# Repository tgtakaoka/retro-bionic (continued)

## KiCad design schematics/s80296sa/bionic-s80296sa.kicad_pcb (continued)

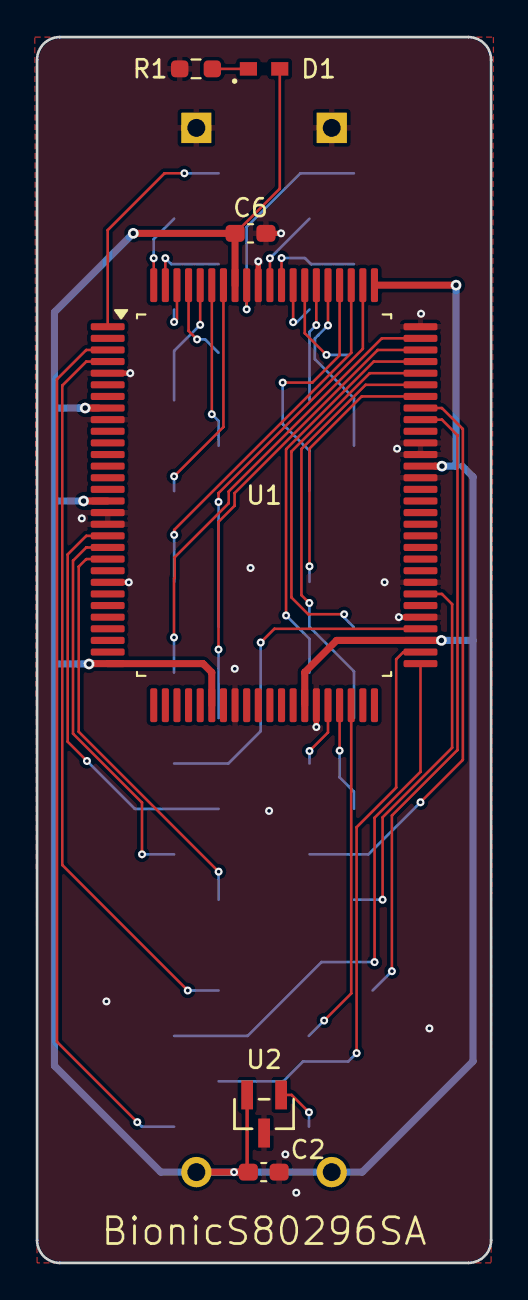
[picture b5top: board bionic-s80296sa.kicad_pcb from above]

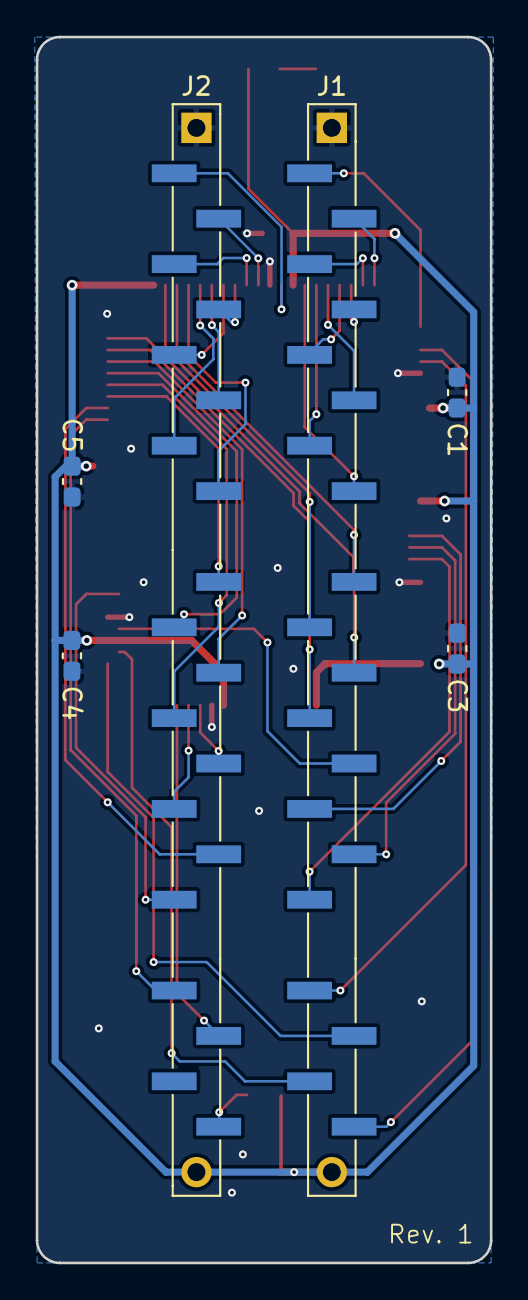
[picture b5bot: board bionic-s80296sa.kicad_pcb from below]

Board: 2 copper layers, 25.4 x 68.6 mm, 12 parts (6 on the bottom side), 42 nets.

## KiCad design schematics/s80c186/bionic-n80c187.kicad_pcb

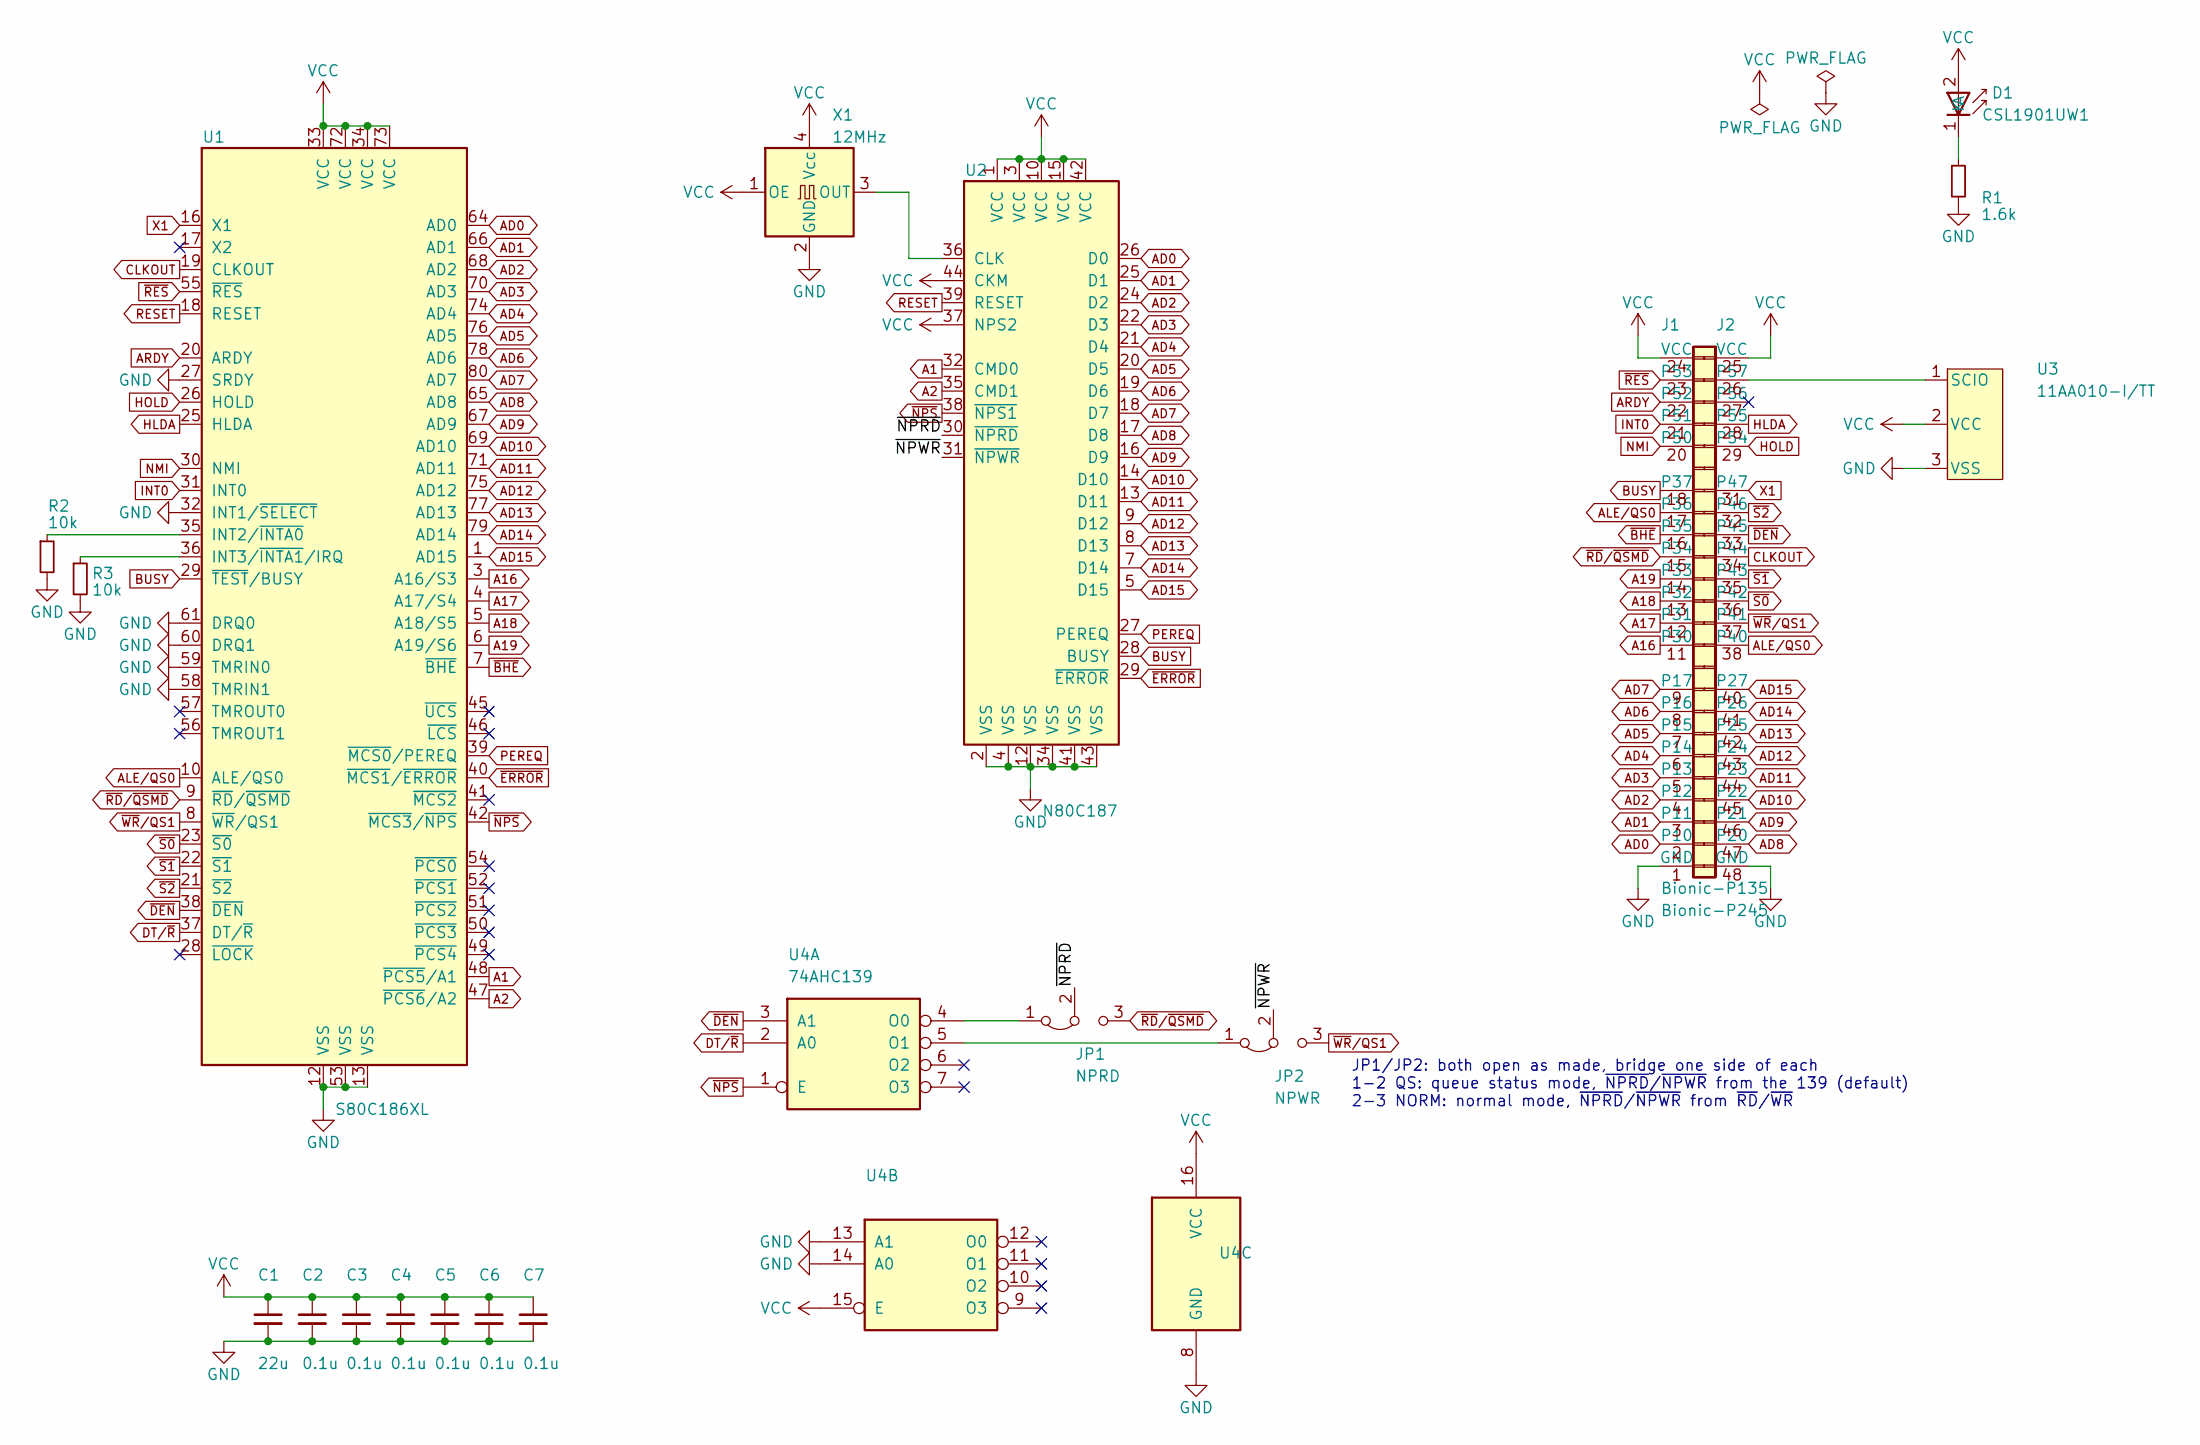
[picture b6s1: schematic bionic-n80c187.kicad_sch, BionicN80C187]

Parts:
C1: 22u; C_0603_1608Metric_Pad1.08x0.95mm_HandSolder
C2, C3, C4, C5, C6, C7: 0.1u; C_0603_1608Metric_Pad1.08x0.95mm_HandSolder
D1: CSL1901UW1; LED_CSL1901UW1_ROM-M
J1: Bionic-P135; Bionic-P135_SMT
J2: Bionic-P245; Bionic-P245_SMT
JP1: NPRD; SolderJumper-3_P2.0mm_Open_TrianglePad1.0x1.5mm_NumberLabels
JP2: NPWR; SolderJumper-3_P2.0mm_Open_TrianglePad1.0x1.5mm_NumberLabels
R1: 1.6k; R_0603_1608Metric_Pad0.98x0.95mm_HandSolder
R2, R3: 10k; R_0603_1608Metric_Pad0.98x0.95mm_HandSolder
U1: S80C186XL; QFP-80_14x20mm_P0.8mm_Intel
U2: N80C187; PLCC-44_SMD-Socket
U3: 11AA010-I/TT; SOT-23_MC_MCH-M
U4: 74AHC139; TSSOP-16_4.4x5mm_P0.65mm
X1: 12MHz; SX3M_3.2x2.5mm_HandSoldering

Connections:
/~NPRD: JP1.2 (C), U2.30 (~NPRD)
/~NPWR: JP2.2 (C), U2.31 (~NPWR)
A1: U1.48 (~PCS5/A1), U2.32 (CMD0)
A2: U1.47 (~PCS6/A2), U2.35 (CMD1)
A16: J1.11 (P30), U1.3 (A16/S3)
A17: J1.12 (P31), U1.4 (A17/S4)
A18: J1.13 (P32), U1.5 (A18/S5)
A19: J1.14 (P33), U1.6 (A19/S6)
AD0: J1.2 (P10), U1.64 (AD0), U2.26 (D0)
AD1: J1.3 (P11), U1.66 (AD1), U2.25 (D1)
AD2: J1.4 (P12), U1.68 (AD2), U2.24 (D2)
AD3: J1.5 (P13), U1.70 (AD3), U2.22 (D3)
AD4: J1.6 (P14), U1.74 (AD4), U2.21 (D4)
AD5: J1.7 (P15), U1.76 (AD5), U2.20 (D5)
AD6: J1.8 (P16), U1.78 (AD6), U2.19 (D6)
AD7: J1.9 (P17), U1.80 (AD7), U2.18 (D7)
AD8: J2.47 (P20), U1.65 (AD8), U2.17 (D8)
AD9: J2.46 (P21), U1.67 (AD9), U2.16 (D9)
AD10: J2.45 (P22), U1.69 (AD10), U2.14 (D10)
AD11: J2.44 (P23), U1.71 (AD11), U2.13 (D11)
AD12: J2.43 (P24), U1.75 (AD12), U2.9 (D12)
AD13: J2.42 (P25), U1.77 (AD13), U2.8 (D13)
AD14: J2.41 (P26), U1.79 (AD14), U2.7 (D14)
AD15: J2.40 (P27), U1.1 (AD15), U2.5 (D15)
ALE/QS0: J1.17 (P36), J2.38 (P40), U1.10 (ALE/QS0)
ARDY: J1.22 (P52), U1.20 (ARDY)
BUSY: J1.18 (P37), U1.29 (~TEST/BUSY), U2.28 (BUSY)
CLKOUT: J2.34 (P44), U1.19 (CLKOUT)
DT/~R: U1.37 (DT/~R), U4.2 (A0)
GND: C1.2, C2.2, C3.2, C4.2, C5.2, C6.2, C7.2, J1.1 (GND), J2.48 (GND), R1.2, R2.2, R3.2, U1.12 (VSS), U1.13 (VSS), U1.27 (SRDY), U1.32 (INT1/~SELECT), U1.53 (VSS), U1.58 (TMRIN1), U1.59 (TMRIN0), U1.60 (DRQ1), U1.61 (DRQ0), U2.2 (VSS), U2.4 (VSS), U2.12 (VSS), U2.34 (VSS), U2.41 (VSS), U2.43 (VSS), U3.3 (VSS), U4.8 (GND), U4.13 (A1), U4.14 (A0), X1.2 (GND)
HLDA: J2.28 (P55), U1.25 (HLDA)
HOLD: J2.29 (P54), U1.26 (HOLD)
INT0: J1.21 (P51), U1.31 (INT0)
NMI: J1.20 (P50), U1.30 (NMI)
unnamed: D1.1 (K), R1.1
unnamed: J2.26 (P57), U3.1 (SCIO)
unnamed: JP1.1 (A), U4.4 (O0)
unnamed: JP2.1 (A), U4.5 (O1)
unnamed: R2.1, U1.35 (INT2/~INTA0)
unnamed: R3.1, U1.36 (INT3/~INTA1/IRQ)
unnamed: U2.36 (CLK), X1.3 (OUT)
PEREQ: U1.39 (~MCS0/PEREQ), U2.27 (PEREQ)
RESET: U1.18 (RESET), U2.39 (RESET)
VCC: C1.1, C2.1, C3.1, C4.1, C5.1, C6.1, C7.1, D1.2 (A), J1.24 (VCC), J2.25 (VCC), U1.33 (VCC), U1.34 (VCC), U1.72 (VCC), U1.73 (VCC), U2.1 (VCC), U2.3 (VCC), U2.10 (VCC), U2.15 (VCC), U2.37 (NPS2), U2.42 (VCC), U2.44 (CKM), U3.2 (VCC), U4.15 (E), U4.16 (VCC), X1.1 (OE), X1.4 (Vcc)
X1: J2.31 (P47), U1.16 (X1)
~BHE: J1.16 (P35), U1.7 (~BHE)
~DEN: J2.33 (P45), U1.38 (~DEN), U4.3 (A1)
~ERROR: U1.40 (~MCS1/~ERROR), U2.29 (~ERROR)
~NPS: U1.42 (~MCS3/~NPS), U2.38 (~NPS1), U4.1 (E)
~RD/~QSMD: J1.15 (P34), JP1.3 (B), U1.9 (~RD/~QSMD)
~RES: J1.23 (P53), U1.55 (~RES)
~S0: J2.36 (P42), U1.23 (~S0)
~S1: J2.35 (P43), U1.22 (~S1)
~S2: J2.32 (P46), U1.21 (~S2)
~WR/QS1: J2.37 (P41), JP2.3 (B), U1.8 (~WR/QS1)

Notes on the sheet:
JP1/JP2: both open as made, bridge one side of each 1-2 QS: queue status mode, ~{NPRD}/~{NPWR} from the 139 (default) 2-3 NORM: normal mode, ~{NPRD}/~{NPWR} from ~{RD}/~{WR}

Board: 4 copper layers, 20 parts (12 on the bottom side), 55 nets, no tracks yet.

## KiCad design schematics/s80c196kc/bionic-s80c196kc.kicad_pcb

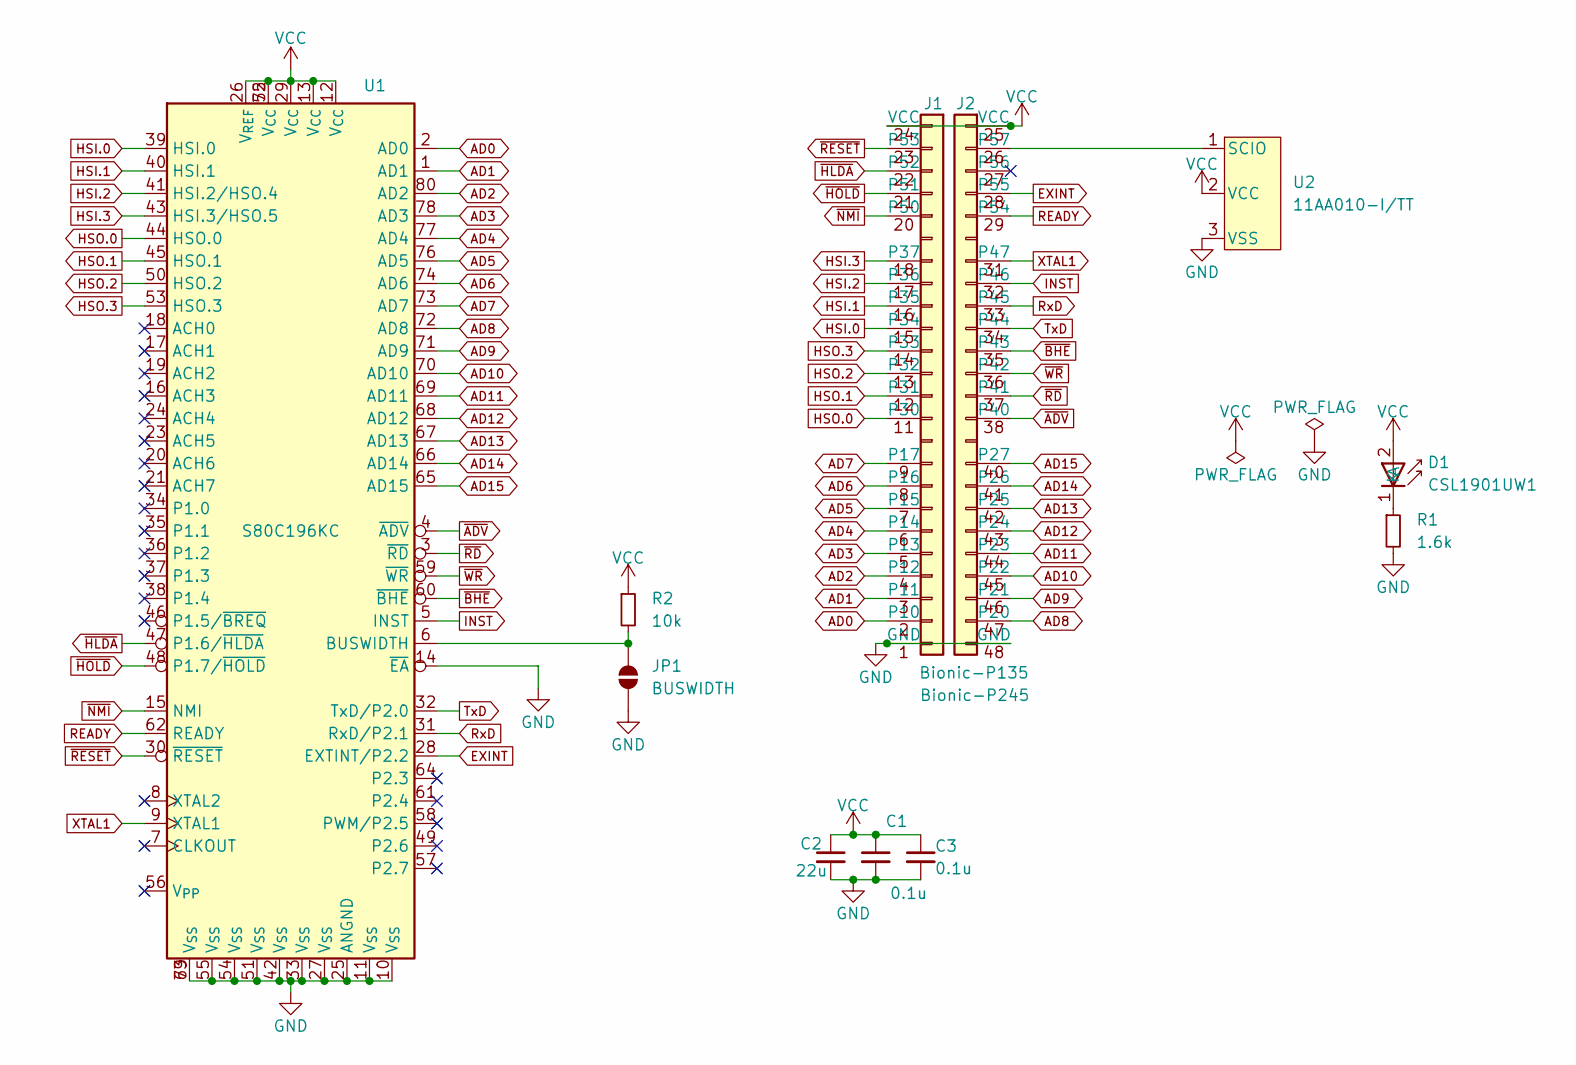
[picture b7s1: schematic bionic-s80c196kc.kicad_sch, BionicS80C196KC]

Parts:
C1, C3: 0.1u; C_0603_1608Metric_Pad1.08x0.95mm_HandSolder
C2: 22u; C_0603_1608Metric_Pad1.08x0.95mm_HandSolder
D1: CSL1901UW1; LED_CSL1901UW1_ROM-M
J1: Bionic-P135; Bionic-P135_SMT
J2: Bionic-P245; Bionic-P245_SMT
JP1: BUSWIDTH; SolderJumper-2_P1.3mm_Open_TrianglePad1.0x1.5mm
R1: 1.6k; R_0603_1608Metric_Pad0.98x0.95mm_HandSolder
R2: 10k; R_0603_1608Metric_Pad0.98x0.95mm_HandSolder
U1: S80C196KC; PQFP-80_14x20mm_P0.8mm
U2: 11AA010-I/TT; SOT-23_MC_MCH-M

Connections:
AD0: J1.2 (P10), U1.2 (AD0)
AD1: J1.3 (P11), U1.1 (AD1)
AD2: J1.4 (P12), U1.80 (AD2)
AD3: J1.5 (P13), U1.78 (AD3)
AD4: J1.6 (P14), U1.77 (AD4)
AD5: J1.7 (P15), U1.76 (AD5)
AD6: J1.8 (P16), U1.74 (AD6)
AD7: J1.9 (P17), U1.73 (AD7)
AD8: J2.47 (P20), U1.72 (AD8)
AD9: J2.46 (P21), U1.71 (AD9)
AD10: J2.45 (P22), U1.70 (AD10)
AD11: J2.44 (P23), U1.69 (AD11)
AD12: J2.43 (P24), U1.68 (AD12)
AD13: J2.42 (P25), U1.67 (AD13)
AD14: J2.41 (P26), U1.66 (AD14)
AD15: J2.40 (P27), U1.65 (AD15)
EXINT: J2.28 (P55), U1.28 (EXTINT/P2.2)
GND: C1.2, C2.2, C3.2, J1.1 (GND), J2.48 (GND), JP1.1 (A), R1.2, U1.10 (V_{SS}), U1.11 (V_{SS}), U1.14 (~EA), U1.25 (ANGND), U1.27 (V_{SS}), U1.33 (V_{SS}), U1.42 (V_{SS}), U1.51 (V_{SS}), U1.54 (V_{SS}), U1.55 (V_{SS}), U1.63 (V_{SS}), U1.79 (V_{SS}), U2.3 (VSS)
HSI.0: J1.15 (P34), U1.39 (HSI.0)
HSI.1: J1.16 (P35), U1.40 (HSI.1)
HSI.2: J1.17 (P36), U1.41 (HSI.2/HSO.4)
HSI.3: J1.18 (P37), U1.43 (HSI.3/HSO.5)
HSO.0: J1.11 (P30), U1.44 (HSO.0)
HSO.1: J1.12 (P31), U1.45 (HSO.1)
HSO.2: J1.13 (P32), U1.50 (HSO.2)
HSO.3: J1.14 (P33), U1.53 (HSO.3)
INST: J2.32 (P46), U1.5 (INST)
unnamed: D1.1 (K), R1.1
unnamed: J2.26 (P57), U2.1 (SCIO)
unnamed: JP1.2 (B), R2.2, U1.6 (BUSWIDTH)
READY: J2.29 (P54), U1.62 (READY)
RxD: J2.33 (P45), U1.31 (RxD/P2.1)
TxD: J2.34 (P44), U1.32 (TxD/P2.0)
VCC: C1.1, C2.1, C3.1, D1.2 (A), J1.24 (VCC), J2.25 (VCC), R2.1, U1.12 (V_{CC}), U1.13 (V_{CC}), U1.26 (V_{REF}), U1.29 (V_{CC}), U1.52 (V_{CC}), U1.75 (V_{CC}), U2.2 (VCC)
XTAL1: J2.31 (P47), U1.9 (XTAL1)
~ADV: J2.38 (P40), U1.4 (~ADV)
~BHE: J2.35 (P43), U1.60 (~BHE)
~HLDA: J1.22 (P52), U1.47 (P1.6/~HLDA)
~HOLD: J1.21 (P51), U1.48 (P1.7/~HOLD)
~NMI: J1.20 (P50), U1.15 (NMI)
~RD: J2.37 (P41), U1.3 (~RD)
~RESET: J1.23 (P53), U1.30 (~RESET)
~WR: J2.36 (P42), U1.59 (~WR)

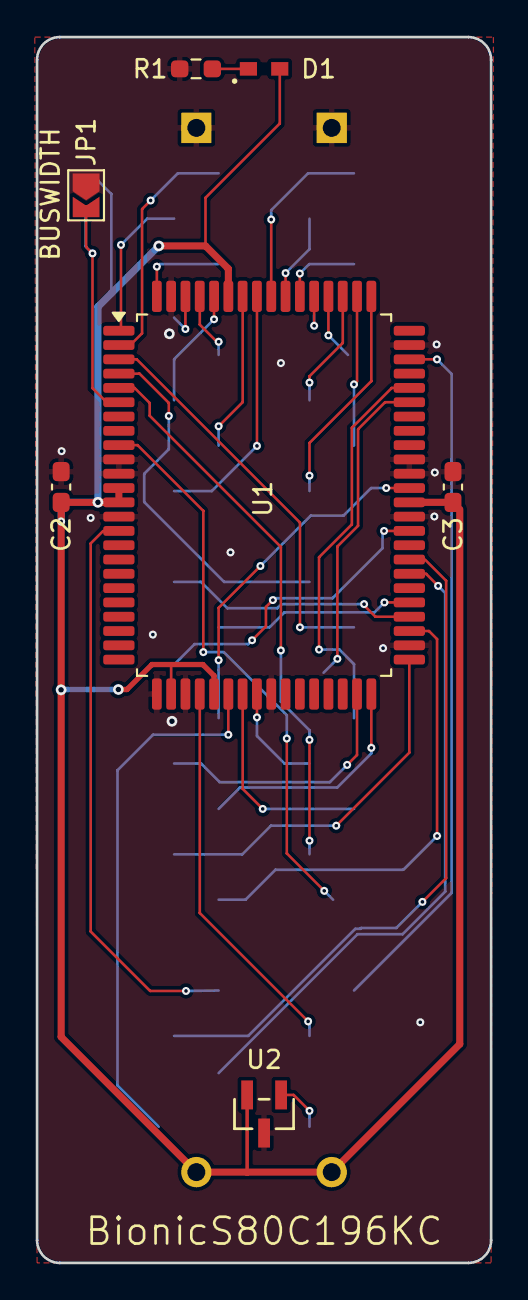
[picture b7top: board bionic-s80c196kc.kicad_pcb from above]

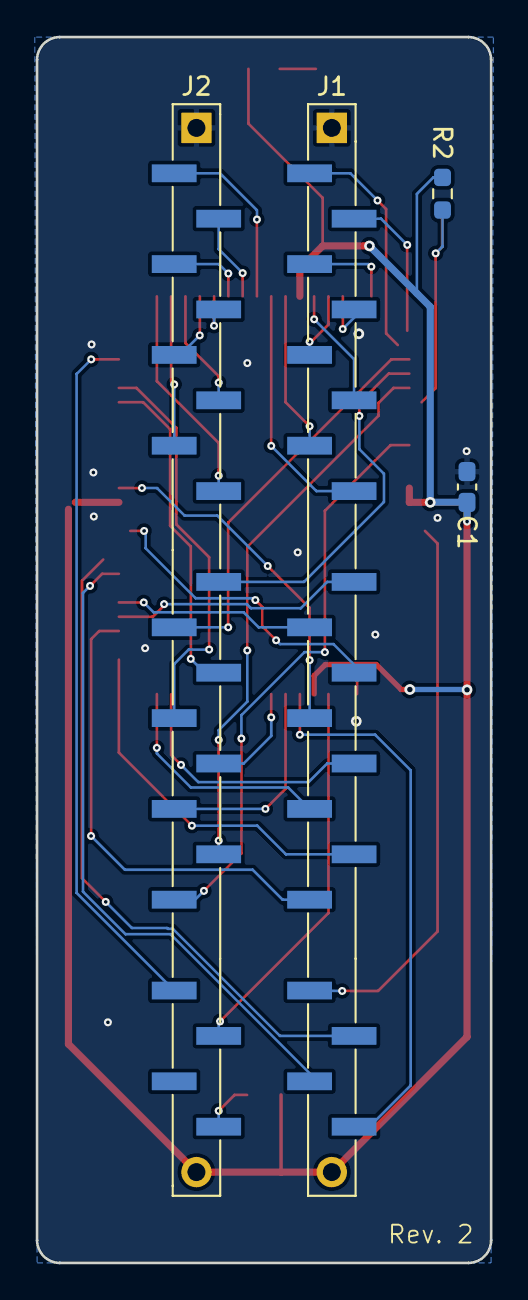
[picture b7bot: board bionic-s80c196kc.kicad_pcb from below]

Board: 2 copper layers, 25.4 x 68.6 mm, 11 parts (4 on the bottom side), 43 nets.
